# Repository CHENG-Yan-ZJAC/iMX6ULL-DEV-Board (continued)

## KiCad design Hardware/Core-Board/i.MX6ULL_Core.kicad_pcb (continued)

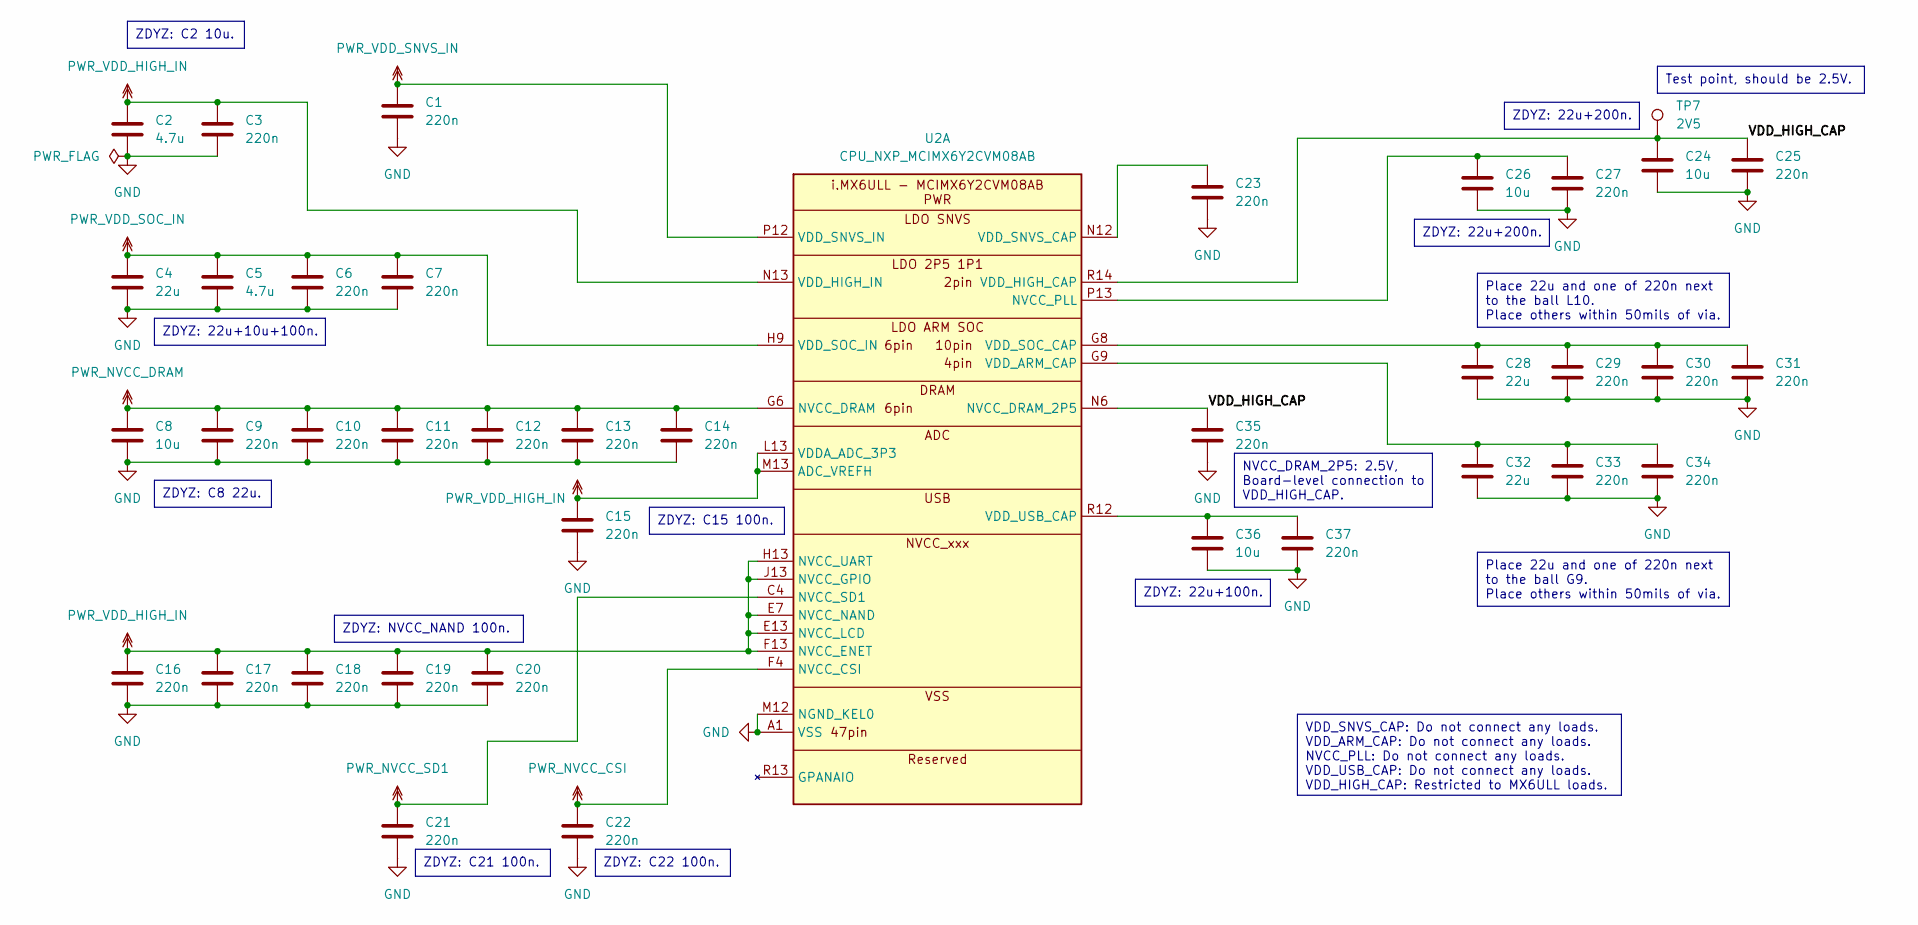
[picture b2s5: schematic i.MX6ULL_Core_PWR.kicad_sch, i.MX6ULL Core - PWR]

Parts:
C1, C3, C6, C7, C9, C10, C11, C12, C13, C14, C15, C16, C17, C18, C19, C20, C21, C22, C23, C25, C27, C29, C30, C31, C33, C34, C35, C37: 220n; C_0402
C2, C5: 4.7u; C_0402
C4, C28, C32: 22u; C_0402
C8, C24, C26, C36: 10u; C_0402
TP7: 2V5; TestPoint_Pad_D1.0mm
U2: CPU_NXP_MCIMX6Y2CVM08AB; NXP_BGA-289_14x14mm_Layout14x14_P0.8mm_Ball0.45mm_Pad0.4mm

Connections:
/PWR/VDD_HIGH_CAP: C24.2, C25.2, C35.2, TP7.1, U2.N6 (NVCC_DRAM_2P5), U2.R14 (VDD_HIGH_CAP), U2.R15 (VDD_HIGH_CAP)
GND: C1.2, C2.1, C3.1, C4.1, C5.1, C6.1, C7.2, C8.1, C9.1, C10.1, C11.1, C12.1, C13.1, C14.1, C15.1, C16.1, C17.2, C18.2, C19.2, C20.2, C21.2, C22.2, C23.1, C24.1, C25.1, C26.2, C27.2, C28.2, C29.2, C30.2, C31.2, C32.1, C33.1, C34.1, C35.1, C36.2, C37.2, U2.A1 (VSS), U2.A17 (VSS), U2.C3 (VSS), U2.C7 (VSS), U2.C11 (VSS), U2.C15 (VSS), U2.E8 (VSS), U2.E11 (VSS), U2.F6 (VSS), U2.F7 (VSS), U2.F8 (VSS), U2.F9 (VSS), U2.F10 (VSS), U2.F11 (VSS), U2.F12 (VSS), U2.G3 (VSS), U2.G5 (VSS), U2.G7 (VSS), U2.G12 (VSS), U2.G15 (VSS), U2.H7 (VSS), U2.H12 (VSS), U2.J5 (VSS), U2.J7 (VSS), U2.J12 (VSS), U2.K7 (VSS), U2.K12 (VSS), U2.L3 (VSS), U2.L7 (VSS), U2.L12 (VSS), U2.M7 (VSS), U2.M8 (VSS), U2.M9 (VSS), U2.M10 (VSS), U2.M11 (VSS), U2.M12 (NGND_KEL0), U2.N3 (VSS), U2.N5 (VSS), U2.R3 (VSS), U2.R5 (VSS), U2.R7 (VSS), U2.R11 (VSS), U2.R16 (VSS), U2.R17 (VSS), U2.T14 (VSS), U2.U1 (VSS), U2.U14 (VSS), U2.U17 (VSS); also elsewhere on the board
unnamed: C28.1, C29.1, C30.1, C31.1, U2.G8 (VDD_SOC_CAP), U2.H8 (VDD_SOC_CAP), U2.J8 (VDD_SOC_CAP), U2.J11 (VDD_SOC_CAP), U2.K8 (VDD_SOC_CAP), U2.K11 (VDD_SOC_CAP), U2.L8 (VDD_SOC_CAP), U2.L9 (VDD_SOC_CAP), U2.L10 (VDD_SOC_CAP), U2.L11 (VDD_SOC_CAP)
unnamed: C32.2, C33.2, C34.2, U2.G9 (VDD_ARM_CAP), U2.G10 (VDD_ARM_CAP), U2.G11 (VDD_ARM_CAP), U2.H11 (VDD_ARM_CAP)
unnamed: C26.1, C27.1, U2.P13 (NVCC_PLL)
unnamed: C23.2, U2.N12 (VDD_SNVS_CAP)
unnamed: C36.1, C37.1, U2.R12 (VDD_USB_CAP)
PWR_NVCC_CSI: C22.1, U2.F4 (NVCC_CSI); also elsewhere on the board
PWR_NVCC_DRAM: C8.2, C9.2, C10.2, C11.2, C12.2, C13.2, C14.2, U2.G6 (NVCC_DRAM), U2.H6 (NVCC_DRAM), U2.J6 (NVCC_DRAM), U2.K6 (NVCC_DRAM), U2.L6 (NVCC_DRAM), U2.M6 (NVCC_DRAM); also elsewhere on the board
PWR_NVCC_SD1: C21.1, U2.C4 (NVCC_SD1); also elsewhere on the board
PWR_VDD_HIGH_IN: C2.2, C3.2, C15.2, C16.2, C17.1, C18.1, C19.1, C20.1, U2.E7 (NVCC_NAND), U2.E13 (NVCC_LCD), U2.F13 (NVCC_ENET), U2.H13 (NVCC_UART), U2.J13 (NVCC_GPIO), U2.L13 (VDDA_ADC_3P3), U2.M13 (ADC_VREFH), U2.N13 (VDD_HIGH_IN); also elsewhere on the board
PWR_VDD_SNVS_IN: C1.1, U2.P12 (VDD_SNVS_IN); also elsewhere on the board
PWR_VDD_SOC_IN: C4.2, C5.2, C6.2, C7.1, U2.H9 (VDD_SOC_IN), U2.H10 (VDD_SOC_IN), U2.J9 (VDD_SOC_IN), U2.J10 (VDD_SOC_IN), U2.K9 (VDD_SOC_IN), U2.K10 (VDD_SOC_IN); also elsewhere on the board

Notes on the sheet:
ZDYZ: 22u+10u+100n.
NVCC_DRAM_2P5: 2.5V, Board-level connection to VDD_HIGH_CAP.
ZDYZ: C15 100n.
ZDYZ: C22 100n.
ZDYZ: C21 100n.
VDD_SNVS_CAP: Do not connect any loads. VDD_ARM_CAP: Do not connect any loads. NVCC_PLL: Do not connect any loads. VDD_USB_CAP: Do not connect any loads. VDD_HIGH_CAP: Restricted to MX6ULL loads.
ZDYZ: C2 10u.
ZDYZ: NVCC_NAND 100n.
ZDYZ: 22u+200n.
ZDYZ: 22u+100n.
Place 22u and one of 220n next to the ball L10. Place others within 50mils of via.
Place 22u and one of 220n next to the ball G9. Place others within 50mils of via.
ZDYZ: C8 22u.
Test point, should be 2.5V.

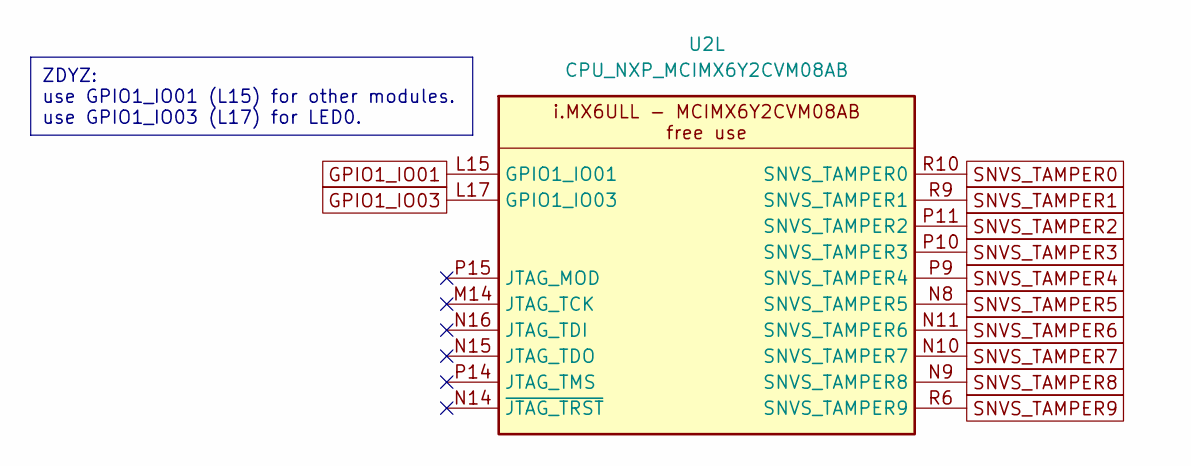
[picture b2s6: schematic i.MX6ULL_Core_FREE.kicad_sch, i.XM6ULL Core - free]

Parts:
U2: CPU_NXP_MCIMX6Y2CVM08AB; NXP_BGA-289_14x14mm_Layout14x14_P0.8mm_Ball0.45mm_Pad0.4mm

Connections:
GPIO1_IO01: U2.L15 (GPIO1_IO01); also elsewhere on the board
GPIO1_IO03: U2.L17 (GPIO1_IO03); also elsewhere on the board
SNVS_TAMPER0: U2.R10 (SNVS_TAMPER0); also elsewhere on the board
SNVS_TAMPER1: U2.R9 (SNVS_TAMPER1); also elsewhere on the board
SNVS_TAMPER2: U2.P11 (SNVS_TAMPER2); also elsewhere on the board
SNVS_TAMPER3: U2.P10 (SNVS_TAMPER3); also elsewhere on the board
SNVS_TAMPER4: U2.P9 (SNVS_TAMPER4); also elsewhere on the board
SNVS_TAMPER5: U2.N8 (SNVS_TAMPER5); also elsewhere on the board
SNVS_TAMPER6: U2.N11 (SNVS_TAMPER6); also elsewhere on the board
SNVS_TAMPER7: U2.N10 (SNVS_TAMPER7); also elsewhere on the board
SNVS_TAMPER8: U2.N9 (SNVS_TAMPER8); also elsewhere on the board
SNVS_TAMPER9: U2.R6 (SNVS_TAMPER9); also elsewhere on the board

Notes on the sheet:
ZDYZ: use GPIO1_IO01 (L15) for other modules. use GPIO1_IO03 (L17) for LED0.

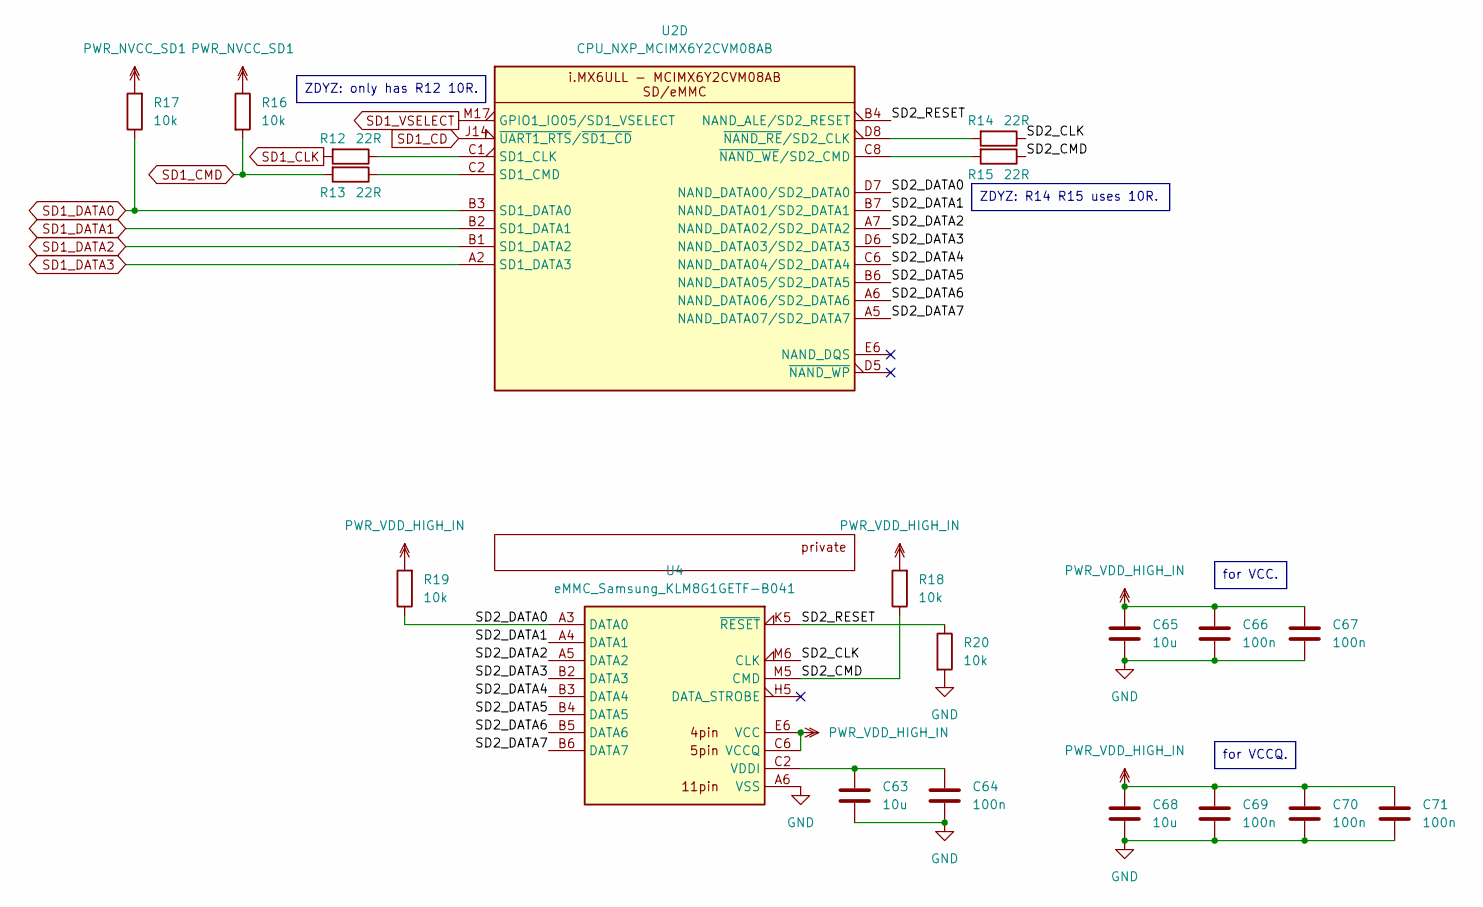
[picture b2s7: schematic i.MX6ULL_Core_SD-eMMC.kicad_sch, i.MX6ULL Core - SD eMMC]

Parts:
C63, C65, C68: 10u; C_0402
C64, C66, C67, C69, C70, C71: 100n; C_0402
R12, R13, R14, R15: 22R; R_0402
R16, R17, R18, R19, R20: 10k; R_0402
U2: CPU_NXP_MCIMX6Y2CVM08AB; NXP_BGA-289_14x14mm_Layout14x14_P0.8mm_Ball0.45mm_Pad0.4mm
U4: eMMC_Samsung_KLM8G1GETF-B041; Samsung_BGA-153_11.5x13mm_Layout11.5x13_P0.5mm_Ball0.3mm_Pa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

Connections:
/SD-eMMC/SD2_CLK: R14.1, U4.M6 (CLK)
/SD-eMMC/SD2_CMD: R15.1, R18.1, U4.M5 (CMD)
/SD-eMMC/SD2_DATA0: R19.1, U2.D7 (NAND_DATA00/SD2_DATA0), U4.A3 (DATA0)
/SD-eMMC/SD2_DATA1: U2.B7 (NAND_DATA01/SD2_DATA1), U4.A4 (DATA1)
/SD-eMMC/SD2_DATA2: U2.A7 (NAND_DATA02/SD2_DATA2), U4.A5 (DATA2)
/SD-eMMC/SD2_DATA3: U2.D6 (NAND_DATA03/SD2_DATA3), U4.B2 (DATA3)
/SD-eMMC/SD2_DATA4: U2.C6 (NAND_DATA04/SD2_DATA4), U4.B3 (DATA4)
/SD-eMMC/SD2_DATA5: U2.B6 (NAND_DATA05/SD2_DATA5), U4.B4 (DATA5)
/SD-eMMC/SD2_DATA6: U2.A6 (NAND_DATA06/SD2_DATA6), U4.B5 (DATA6)
/SD-eMMC/SD2_DATA7: U2.A5 (NAND_DATA07/SD2_DATA7), U4.B6 (DATA7)
/SD-eMMC/SD2_RESET: R20.1, U2.B4 (NAND_ALE/SD2_RESET), U4.K5 (~RESET)
GND: C63.2, C64.2, C65.2, C66.2, C67.2, C68.2, C69.2, C70.2, C71.2, R20.2, U4.A6 (VSS), U4.C4 (VSS), U4.E7 (VSS), U4.G5 (VSS), U4.H10 (VSS), U4.J5 (VSS), U4.K8 (VSS), U4.N2 (VSS), U4.N5 (VSS), U4.P4 (VSS), U4.P6 (VSS); also elsewhere on the board
unnamed: R12.1, U2.C1 (SD1_CLK)
unnamed: R13.1, U2.C2 (SD1_CMD)
unnamed: R14.2, U2.D8 (~NAND_RE/SD2_CLK)
unnamed: R15.2, U2.C8 (~NAND_WE/SD2_CMD)
unnamed: C63.1, C64.1, U4.C2 (VDDI)
PWR_NVCC_SD1: R16.1, R17.2; also elsewhere on the board
PWR_VDD_HIGH_IN: C65.1, C66.1, C67.1, C68.1, C69.1, C70.1, C71.1, R18.2, R19.2, U4.C6 (VCCQ), U4.E6 (VCC), U4.F5 (VCC), U4.J10 (VCC), U4.K9 (VCC), U4.M4 (VCCQ), U4.N4 (VCCQ), U4.P3 (VCCQ), U4.P5 (VCCQ); also elsewhere on the board
SD1_CD: U2.J14 (~UART1_RTS/~SD1_CD); also elsewhere on the board
SD1_CLK: R12.2; also elsewhere on the board
SD1_CMD: R13.2, R16.2; also elsewhere on the board
SD1_DATA0: R17.1, U2.B3 (SD1_DATA0); also elsewhere on the board
SD1_DATA1: U2.B2 (SD1_DATA1); also elsewhere on the board
SD1_DATA2: U2.B1 (SD1_DATA2); also elsewhere on the board
SD1_DATA3: U2.A2 (SD1_DATA3); also elsewhere on the board
SD1_VSELECT: U2.M17 (GPIO1_IO05/SD1_VSELECT); also elsewhere on the board

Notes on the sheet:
for VCC.
ZDYZ: only has R12 10R.
for VCCQ.
ZDYZ: R14 R15 uses 10R.

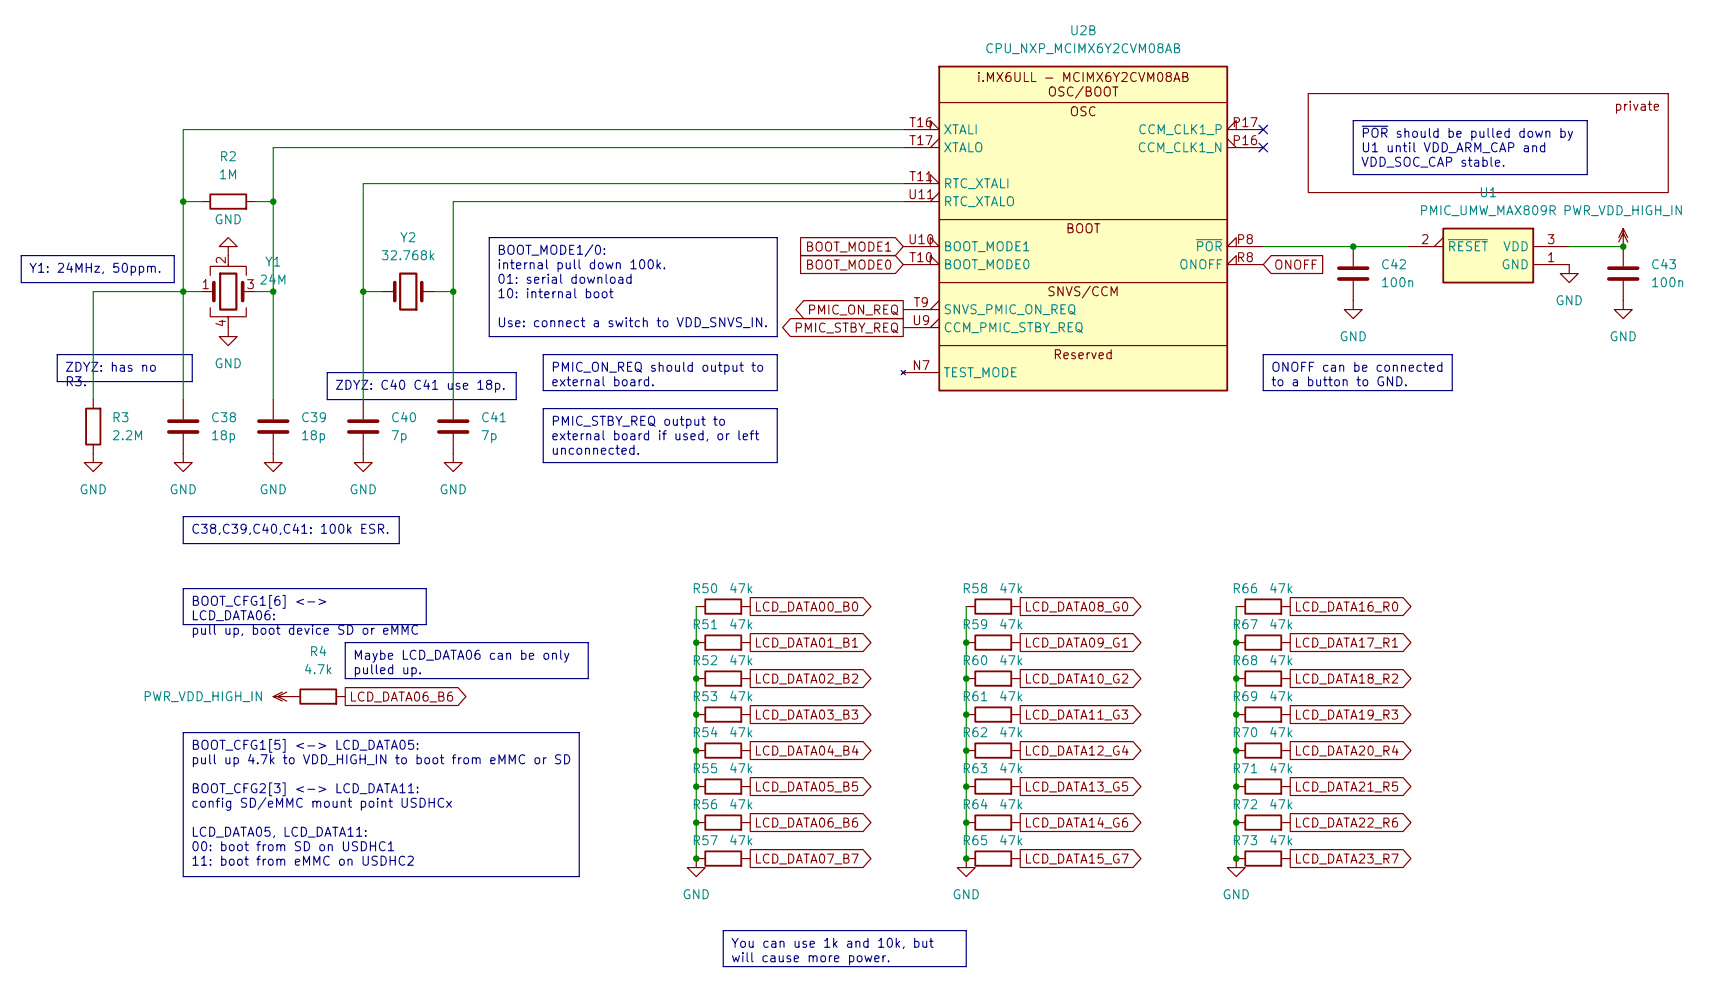
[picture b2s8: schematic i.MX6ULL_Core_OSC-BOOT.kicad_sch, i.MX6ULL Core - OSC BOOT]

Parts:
C38, C39: 18p; C_0402
C40, C41: 7p; C_0402
C42, C43: 100n; C_0402
R2: 1M; R_0402
R3: 2.2M; R_0402
R4: 4.7k; R_0402
R50, R51, R52, R53, R54, R55, R56, R57, R58, R59, R60, R61, R62, R63, R64, R65, R66, R67, R68, R69, R70, R71, R72, R73: 47k; R_0402
U1: PMIC_UMW_MAX809R; SOT_23
U2: CPU_NXP_MCIMX6Y2CVM08AB; NXP_BGA-289_14x14mm_Layout14x14_P0.8mm_Ball0.45mm_Pad0.4mm
Y1: 24M; Crystal_SMD_3225-4Pin_3.2x2.5mm
Y2: 32.768k; Crystal_SMD_3215-2Pin_3.2x1.5mm

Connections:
BOOT_MODE0: U2.T10 (BOOT_MODE0); also elsewhere on the board
BOOT_MODE1: U2.U10 (BOOT_MODE1); also elsewhere on the board
GND: C38.1, C39.2, C40.1, C41.2, C42.2, C43.1, R3.1, R50.1, R51.1, R52.1, R53.1, R54.1, R55.1, R56.1, R57.1, R58.1, R59.1, R60.1, R61.1, R62.1, R63.1, R64.1, R65.1, R66.1, R67.1, R68.1, R69.1, R70.1, R71.1, R72.1, R73.1, U1.1 (GND), Y1.2, Y1.4; also elsewhere on the board
LCD_DATA00_B0: R50.2; also elsewhere on the board
LCD_DATA01_B1: R51.2; also elsewhere on the board
LCD_DATA02_B2: R52.2; also elsewhere on the board
LCD_DATA03_B3: R53.2; also elsewhere on the board
LCD_DATA04_B4: R54.2; also elsewhere on the board
LCD_DATA05_B5: R55.2; also elsewhere on the board
LCD_DATA06_B6: R4.2, R56.2; also elsewhere on the board
LCD_DATA07_B7: R57.2; also elsewhere on the board
LCD_DATA08_G0: R58.2; also elsewhere on the board
LCD_DATA09_G1: R59.2; also elsewhere on the board
LCD_DATA10_G2: R60.2; also elsewhere on the board
LCD_DATA11_G3: R61.2; also elsewhere on the board
LCD_DATA12_G4: R62.2; also elsewhere on the board
LCD_DATA13_G5: R63.2; also elsewhere on the board
LCD_DATA14_G6: R64.2; also elsewhere on the board
LCD_DATA15_G7: R65.2; also elsewhere on the board
LCD_DATA16_R0: R66.2; also elsewhere on the board
LCD_DATA17_R1: R67.2; also elsewhere on the board
LCD_DATA18_R2: R68.2; also elsewhere on the board
LCD_DATA19_R3: R69.2; also elsewhere on the board
LCD_DATA20_R4: R70.2; also elsewhere on the board
LCD_DATA21_R5: R71.2; also elsewhere on the board
LCD_DATA22_R6: R72.2; also elsewhere on the board
LCD_DATA23_R7: R73.2; also elsewhere on the board
unnamed: C42.1, U1.2 (~RESET), U2.P8 (~POR)
unnamed: C40.2, U2.T11 (RTC_XTALI), Y2.2
unnamed: C41.1, U2.U11 (RTC_XTALO), Y2.1
unnamed: C38.2, R2.1, R3.2, U2.T16 (XTALI), Y1.1
unnamed: C39.1, R2.2, U2.T17 (XTALO), Y1.3
ONOFF: U2.R8 (ONOFF); also elsewhere on the board
PMIC_ON_REQ: U2.T9 (SNVS_PMIC_ON_REQ); also elsewhere on the board
PMIC_STBY_REQ: U2.U9 (CCM_PMIC_STBY_REQ); also elsewhere on the board
PWR_VDD_HIGH_IN: C43.2, R4.1, U1.3 (VDD); also elsewhere on the board

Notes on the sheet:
ONOFF can be connected to a button to GND.
BOOT_MODE1/0: internal pull down 100k. 01: serial download 10: internal boot Use: connect a switch to VDD_SNVS_IN.
ZDYZ: has no R3.
BOOT_CFG1[5] <-> LCD_DATA05: pull up 4.7k to VDD_HIGH_IN to boot from eMMC or SD BOOT_CFG2[3] <-> LCD_DATA11: config SD/eMMC mount point USDHCx LCD_DATA05, LCD_DATA11: 00: boot from SD on USDHC1 11: boot from eMMC on USDHC2
Y1: 24MHz, 50ppm.
You can use 1k and 10k, but will cause more power.
BOOT_CFG1[6] <-> LCD_DATA06: pull up, boot device SD or eMMC
Maybe LCD_DATA06 can be only pulled up.
PMIC_STBY_REQ output to external board if used, or left unconnected.
ZDYZ: C40 C41 use 18p.
~{POR} should be pulled down by U1 until VDD_ARM_CAP and VDD_SOC_CAP stable.
PMIC_ON_REQ should output to external board.
C38,C39,C40,C41: 100k ESR.

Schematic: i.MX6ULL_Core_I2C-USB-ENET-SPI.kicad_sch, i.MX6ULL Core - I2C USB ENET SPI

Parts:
C72, C73: 1u; C_0402
R22, R23: 10R; R_0402
U2: CPU_NXP_MCIMX6Y2CVM08AB; NXP_BGA-289_14x14mm_Layout14x14_P0.8mm_Ball0.45mm_Pad0.4mm

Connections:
ECSPI3_MISO: U2.A4 (ECSPI3_MISO/NAND_CLE); also elsewhere on the board
ECSPI3_MOSI: U2.B5 (ECSPI3_MOSI/~NAND_CE1); also elsewhere on the board
ECSPI3_SCLK: U2.C5 (ECSPI3_SCLK/~NAND_CE0); also elsewhere on the board
ECSPI3_SS0: U2.A3 (ECSPI3_SS0/~NAND_READY); also elsewhere on the board
ENET1_INT: U2.G14 (GOIO1_IO27/~UART3_RTS); also elsewhere on the board
ENET1_RESET: U2.H14 (GPIO1_IO23/~UART2_RTS); also elsewhere on the board
ENET1_RX_DATA0: U2.F16 (ENET1_RX_DATA0); also elsewhere on the board
ENET1_RX_DATA1: U2.E17 (ENET1_RX_DATA1); also elsewhere on the board
ENET1_RX_EN: U2.E16 (ENET1_RX_EN); also elsewhere on the board
ENET1_RX_ER: U2.D15 (ENET1_RX_ER); also elsewhere on the board
ENET1_TX_CLK: R22.1; also elsewhere on the board
ENET1_TX_DATA0: U2.E15 (ENET1_TX_DATA0); also elsewhere on the board
ENET1_TX_DATA1: U2.E14 (ENET1_TX_DATA1); also elsewhere on the board
ENET1_TX_EN: U2.F15 (ENET1_TX_EN); also elsewhere on the board
ENET2_INT: U2.H15 (~UART3_CTS/GPIO1_IO26); also elsewhere on the board
ENET2_RESET: U2.J15 (~UART2_CTS/GPIO1_IO22); also elsewhere on the board
ENET2_RX_DATA0: U2.C17 (ENET2_RX_DATA0); also elsewhere on the board
ENET2_RX_DATA1: U2.C16 (ENET2_RX_DATA1); also elsewhere on the board
ENET2_RX_EN: U2.B17 (ENET2_RX_EN); also elsewhere on the board
ENET2_RX_ER: U2.D16 (ENET2_RX_ER); also elsewhere on the board
ENET2_TX_CLK: R23.1; also elsewhere on the board
ENET2_TX_DATA0: U2.A15 (ENET2_TX_DATA0); also elsewhere on the board
ENET2_TX_DATA1: U2.A16 (ENET2_TX_DATA1); also elsewhere on the board
ENET2_TX_EN: U2.B15 (ENET2_TX_EN); also elsewhere on the board
ENET_MDC: U2.L16 (ENET_MDC/GPIO1_IO07); also elsewhere on the board
ENET_MDIO: U2.K17 (ENET_MDIO/GPIO1_IO06); also elsewhere on the board
GND: C72.2, C73.2; also elsewhere on the board
I2C1_CLK: U2.G17 (I2C1_CLK/UART4_TXD); also elsewhere on the board
I2C1_SDA: U2.G16 (I2C1_SDA/UART4_RXD); also elsewhere on the board
I2C2_CLK: U2.F17 (UART5_TXD/I2C2_CLK); also elsewhere on the board
I2C2_SDA: U2.G13 (UART5_RXD/I2C2_SDA); also elsewhere on the board
unnamed: R22.2, U2.F14 (ENET1_TX_CLK)
unnamed: R23.2, U2.D17 (ENET2_TX_CLK)
USB_OTG1_DN: U2.T15 (USB_OTG1_DN); also elsewhere on the board
USB_OTG1_DP: U2.U15 (USB_OTG1_DP); also elsewhere on the board
USB_OTG1_ID: U2.K13 (ANATOP_OTG1_ID/GPIO1_IO00); also elsewhere on the board
USB_OTG1_VBUS: C72.1, U2.T12 (USB_OTG1_VBUS); also elsewhere on the board
USB_OTG2_DN: U2.T13 (USB_OTG2_DN); also elsewhere on the board
USB_OTG2_DP: U2.U13 (USB_OTG2_DP); also elsewhere on the board
USB_OTG2_VBUS: C73.1, U2.U12 (USB_OTG2_VBUS); also elsewhere on the board

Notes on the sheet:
ZDYZ: use SNVS_TAMPER8 (N9) for ENET2_RESET. use SNVS_TAMPER6 (N11) for ENET2_INT.
ZDYZ: C73 100n.
C72,C73: 1uF, 10V rated.
ZDYZ: C72 100n.
ZDYZ: use SNVS_TAMPER7 (N10) for ENET1_RESET. use SNVS_TAMPER5 (N8) for ENET1_INT.

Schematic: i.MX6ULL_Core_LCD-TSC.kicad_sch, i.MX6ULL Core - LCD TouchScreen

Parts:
R21: 10R; R_0402
U2: CPU_NXP_MCIMX6Y2CVM08AB; NXP_BGA-289_14x14mm_Layout14x14_P0.8mm_Ball0.45mm_Pad0.4mm

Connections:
LCD_BL_PWM: U2.N17 (GPIO1_IO08/PWM1_OUT); also elsewhere on the board
LCD_CLK: R21.1; also elsewhere on the board
LCD_DATA00_B0: U2.B9 (LCD_DATA00); also elsewhere on the board
LCD_DATA01_B1: U2.A9 (LCD_DATA01); also elsewhere on the board
LCD_DATA02_B2: U2.E10 (LCD_DATA02); also elsewhere on the board
LCD_DATA03_B3: U2.D10 (LCD_DATA03); also elsewhere on the board
LCD_DATA04_B4: U2.C10 (LCD_DATA04); also elsewhere on the board
LCD_DATA05_B5: U2.B10 (LCD_DATA05); also elsewhere on the board
LCD_DATA06_B6: U2.A10 (LCD_DATA06); also elsewhere on the board
LCD_DATA07_B7: U2.D11 (LCD_DATA07); also elsewhere on the board
LCD_DATA08_G0: U2.B11 (LCD_DATA08); also elsewhere on the board
LCD_DATA09_G1: U2.A11 (LCD_DATA09); also elsewhere on the board
LCD_DATA10_G2: U2.E12 (LCD_DATA10); also elsewhere on the board
LCD_DATA11_G3: U2.D12 (LCD_DATA11); also elsewhere on the board
LCD_DATA12_G4: U2.C12 (LCD_DATA12); also elsewhere on the board
LCD_DATA13_G5: U2.B12 (LCD_DATA13); also elsewhere on the board
LCD_DATA14_G6: U2.A12 (LCD_DATA14); also elsewhere on the board
LCD_DATA15_G7: U2.D13 (LCD_DATA15); also elsewhere on the board
LCD_DATA16_R0: U2.C13 (LCD_DATA16); also elsewhere on the board
LCD_DATA17_R1: U2.B13 (LCD_DATA17); also elsewhere on the board
LCD_DATA18_R2: U2.A13 (LCD_DATA18); also elsewhere on the board
LCD_DATA19_R3: U2.D14 (LCD_DATA19); also elsewhere on the board
LCD_DATA20_R4: U2.C14 (LCD_DATA20); also elsewhere on the board
LCD_DATA21_R5: U2.B14 (LCD_DATA21); also elsewhere on the board
LCD_DATA22_R6: U2.A14 (LCD_DATA22); also elsewhere on the board
LCD_DATA23_R7: U2.B16 (LCD_DATA23); also elsewhere on the board
LCD_ENABLE: U2.B8 (LCD_ENABLE); also elsewhere on the board
LCD_HSYNC: U2.D9 (LCD_HSYNC); also elsewhere on the board
LCD_RESET: U2.E9 (LCD_RESET); also elsewhere on the board
LCD_VSYNC: U2.C9 (LCD_VSYNC); also elsewhere on the board
unnamed: R21.2, U2.A8 (LCD_CLK)
TSC_INT: U2.M15 (GPIO1_IO09); also elsewhere on the board
TSC_RESET: U2.L14 (GPIO1_IO02); also elsewhere on the board

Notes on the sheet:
ZDYZ: use LCD_RESET (E9) for reset DCDC_3V3.
ZDYZ: use SNVS_TAMPER9 (R6) for TSC_RESET.

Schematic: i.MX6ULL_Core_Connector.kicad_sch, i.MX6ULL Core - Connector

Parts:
J1: SODIMM-260_DDR4; SODIMM-260_DDR4_Card_edge
M1, M2, M3, M4, M5, M6, M7, M8: MARK_D1.0mm

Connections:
BOOT_MODE0: J1.15; also elsewhere on the board
BOOT_MODE1: J1.17; also elsewhere on the board
CSI_DATA00: J1.106; also elsewhere on the board
CSI_DATA01: J1.110; also elsewhere on the board
CSI_DATA02: J1.112; also elsewhere on the board
CSI_DATA03: J1.108; also elsewhere on the board
CSI_DATA04: J1.104; also elsewhere on the board
CSI_DATA05: J1.100; also elsewhere on the board
CSI_DATA06: J1.98; also elsewhere on the board
CSI_DATA07: J1.94; also elsewhere on the board
CSI_HSYNC: J1.92; also elsewhere on the board
CSI_MCLK: J1.96; also elsewhere on the board
CSI_PIXCLK: J1.102; also elsewhere on the board
CSI_PWDN: J1.90; also elsewhere on the board
CSI_RESET: J1.86; also elsewhere on the board
CSI_VSYNC: J1.88; also elsewhere on the board
ECSPI3_MISO: J1.244; also elsewhere on the board
ECSPI3_MOSI: J1.242; also elsewhere on the board
ECSPI3_SCLK: J1.248; also elsewhere on the board
ECSPI3_SS0: J1.246; also elsewhere on the board
ENET1_INT: J1.66; also elsewhere on the board
ENET1_RESET: J1.64; also elsewhere on the board
ENET1_RX_DATA0: J1.72; also elsewhere on the board
ENET1_RX_DATA1: J1.70; also elsewhere on the board
ENET1_RX_EN: J1.74; also elsewhere on the board
ENET1_RX_ER: J1.82; also elsewhere on the board
ENET1_TX_CLK: J1.68; also elsewhere on the board
ENET1_TX_DATA0: J1.78; also elsewhere on the board
ENET1_TX_DATA1: J1.80; also elsewhere on the board
ENET1_TX_EN: J1.76; also elsewhere on the board
ENET2_INT: J1.65; also elsewhere on the board
ENET2_RESET: J1.63; also elsewhere on the board
ENET2_RX_DATA0: J1.71; also elsewhere on the board
ENET2_RX_DATA1: J1.73; also elsewhere on the board
ENET2_RX_EN: J1.75; also elsewhere on the board
ENET2_RX_ER: J1.69; also elsewhere on the board
ENET2_TX_CLK: J1.67; also elsewhere on the board
ENET2_TX_DATA0: J1.81; also elsewhere on the board
ENET2_TX_DATA1: J1.79; also elsewhere on the board
ENET2_TX_EN: J1.77; also elsewhere on the board
ENET_MDC: J1.59; also elsewhere on the board
ENET_MDIO: J1.61; also elsewhere on the board
GND: J1.21, J1.22, J1.27, J1.28, J1.207, J1.209, J1.211, J1.213, J1.215, J1.217, J1.219, J1.221, J1.223, J1.225, J1.227, J1.229, J1.231, J1.233, J1.235, J1.237; also elsewhere on the board
GPIO1_IO01: J1.54; also elsewhere on the board
GPIO1_IO03: J1.56; also elsewhere on the board
I2C1_CLK: J1.34; also elsewhere on the board
I2C1_SDA: J1.32; also elsewhere on the board
I2C2_CLK: J1.38; also elsewhere on the board
I2C2_SDA: J1.36; also elsewhere on the board
LCD_BL_PWM: J1.121; also elsewhere on the board
LCD_CLK: J1.179; also elsewhere on the board
LCD_DATA00_B0: J1.171; also elsewhere on the board
LCD_DATA01_B1: J1.169; also elsewhere on the board
LCD_DATA02_B2: J1.167; also elsewhere on the board
LCD_DATA03_B3: J1.165; also elsewhere on the board
LCD_DATA04_B4: J1.163; also elsewhere on the board
LCD_DATA05_B5: J1.161; also elsewhere on the board
LCD_DATA06_B6: J1.159; also elsewhere on the board
LCD_DATA07_B7: J1.157; also elsewhere on the board
LCD_DATA08_G0: J1.155; also elsewhere on the board
LCD_DATA09_G1: J1.153; also elsewhere on the board
LCD_DATA10_G2: J1.151; also elsewhere on the board
LCD_DATA11_G3: J1.149; also elsewhere on the board
LCD_DATA12_G4: J1.147; also elsewhere on the board
LCD_DATA13_G5: J1.145; also elsewhere on the board
LCD_DATA14_G6: J1.143; also elsewhere on the board
LCD_DATA15_G7: J1.141; also elsewhere on the board
LCD_DATA16_R0: J1.139; also elsewhere on the board
LCD_DATA17_R1: J1.137; also elsewhere on the board
LCD_DATA18_R2: J1.135; also elsewhere on the board
LCD_DATA19_R3: J1.133; also elsewhere on the board
LCD_DATA20_R4: J1.131; also elsewhere on the board
LCD_DATA21_R5: J1.129; also elsewhere on the board
LCD_DATA22_R6: J1.127; also elsewhere on the board
LCD_DATA23_R7: J1.125; also elsewhere on the board
LCD_ENABLE: J1.173; also elsewhere on the board
LCD_HSYNC: J1.177; also elsewhere on the board
LCD_RESET: J1.123; also elsewhere on the board
LCD_VSYNC: J1.175; also elsewhere on the board
ONOFF: J1.14; also elsewhere on the board
PMIC_ON_REQ: J1.18; also elsewhere on the board
PMIC_STBY_REQ: J1.16; also elsewhere on the board
PWR_NVCC_CSI: J1.220; also elsewhere on the board
PWR_NVCC_DRAM: J1.226, J1.228, J1.230; also elsewhere on the board
PWR_NVCC_SD1: J1.222; also elsewhere on the board
PWR_VDD_HIGH_IN: J1.234, J1.236, J1.238; also elsewhere on the board
PWR_VDD_SNVS_IN: J1.208; also elsewhere on the board
PWR_VDD_SOC_IN: J1.212, J1.214, J1.216; also elsewhere on the board
SD1_CD: J1.241; also elsewhere on the board
SD1_CLK: J1.247; also elsewhere on the board
SD1_CMD: J1.249; also elsewhere on the board
SD1_DATA0: J1.245; also elsewhere on the board
SD1_DATA1: J1.243; also elsewhere on the board
SD1_DATA2: J1.253; also elsewhere on the board
SD1_DATA3: J1.251; also elsewhere on the board
SD1_VSELECT: J1.204; also elsewhere on the board
SNVS_TAMPER0: J1.49; also elsewhere on the board
SNVS_TAMPER1: J1.47; also elsewhere on the board
SNVS_TAMPER2: J1.51; also elsewhere on the board
SNVS_TAMPER3: J1.46; also elsewhere on the board
SNVS_TAMPER4: J1.44; also elsewhere on the board
SNVS_TAMPER5: J1.42; also elsewhere on the board
SNVS_TAMPER6: J1.50; also elsewhere on the board
SNVS_TAMPER7: J1.48; also elsewhere on the board
SNVS_TAMPER8: J1.52; also elsewhere on the board
SNVS_TAMPER9: J1.45; also elsewhere on the board
TSC_INT: J1.119; also elsewhere on the board
TSC_RESET: J1.117; also elsewhere on the board
UART1_RXD: J1.31; also elsewhere on the board
UART1_TXD: J1.33; also elsewhere on the board
UART2_RXD: J1.37; also elsewhere on the board
UART2_TXD: J1.35; also elsewhere on the board
UART3_RXD: J1.41; also elsewhere on the board
UART3_TXD: J1.39; also elsewhere on the board
USB_OTG1_DN: J1.25; also elsewhere on the board
USB_OTG1_DP: J1.23; also elsewhere on the board
USB_OTG1_ID: J1.29; also elsewhere on the board
USB_OTG1_VBUS: J1.19; also elsewhere on the board
USB_OTG2_DN: J1.26; also elsewhere on the board
USB_OTG2_DP: J1.24; also elsewhere on the board
USB_OTG2_VBUS: J1.20; also elsewhere on the board

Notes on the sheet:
8 marks for SMT.

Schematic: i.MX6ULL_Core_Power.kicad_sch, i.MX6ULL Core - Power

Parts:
D1: LED; LED_0402
R1: 1k; R_0402
TP1, TP2: 3V3; TestPoint_Pad_D1.0mm; not fitted
TP3, TP4: 1V35; TestPoint_Pad_D1.0mm; not fitted
TP5: 2V8; TestPoint_Pad_D1.0mm; not fitted
TP6: 3V3,1V8; TestPoint_Pad_D1.0mm; not fitted

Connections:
GND: D1.1 (K); also elsewhere on the board
unnamed: D1.2 (A), R1.1
PWR_VDD_HIGH_IN: R1.2, TP2.1; also elsewhere on the board

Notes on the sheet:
DCDC or LDO
DCDC
+5V
LDO
PWR_VDD_SNVS_IN 3.3V always on
PWR_VDD_SOC_IN 1.35V turned on by PWR_VDD_HIGH_IN
PMIC_ON_REQ
PWR_VDD_HIGH_IN 3.3V turned on by PMIC_ON_REQ
PWR_NVCC_CSI 2.8V turned on by PWR_VDD_HIGH_IN OR LDO from PWR_VDD_HIGH_IN
PWR_NVCC_SD1 3.3V/1.8V turned on by PWR_VDD_HIGH_IN controlled by SD1_VSELECT, switch voltage
PWR_NVCC_DRAM 1.35V turned on by PWR_VDD_HIGH_IN

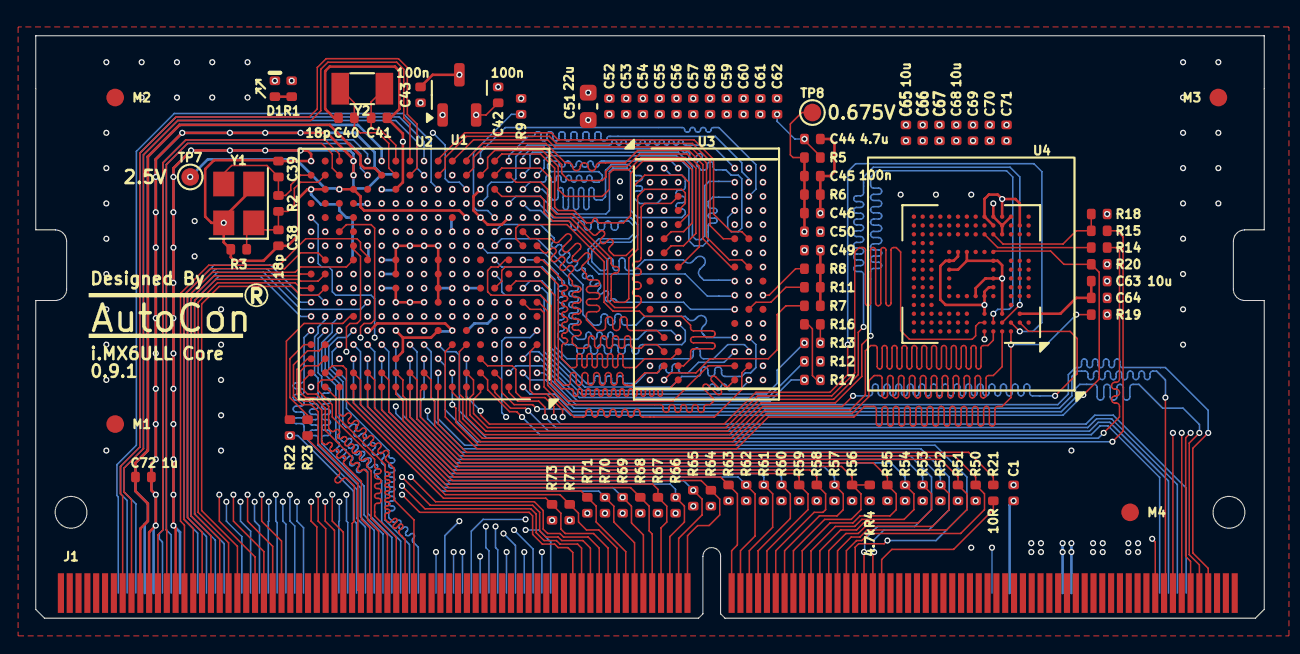
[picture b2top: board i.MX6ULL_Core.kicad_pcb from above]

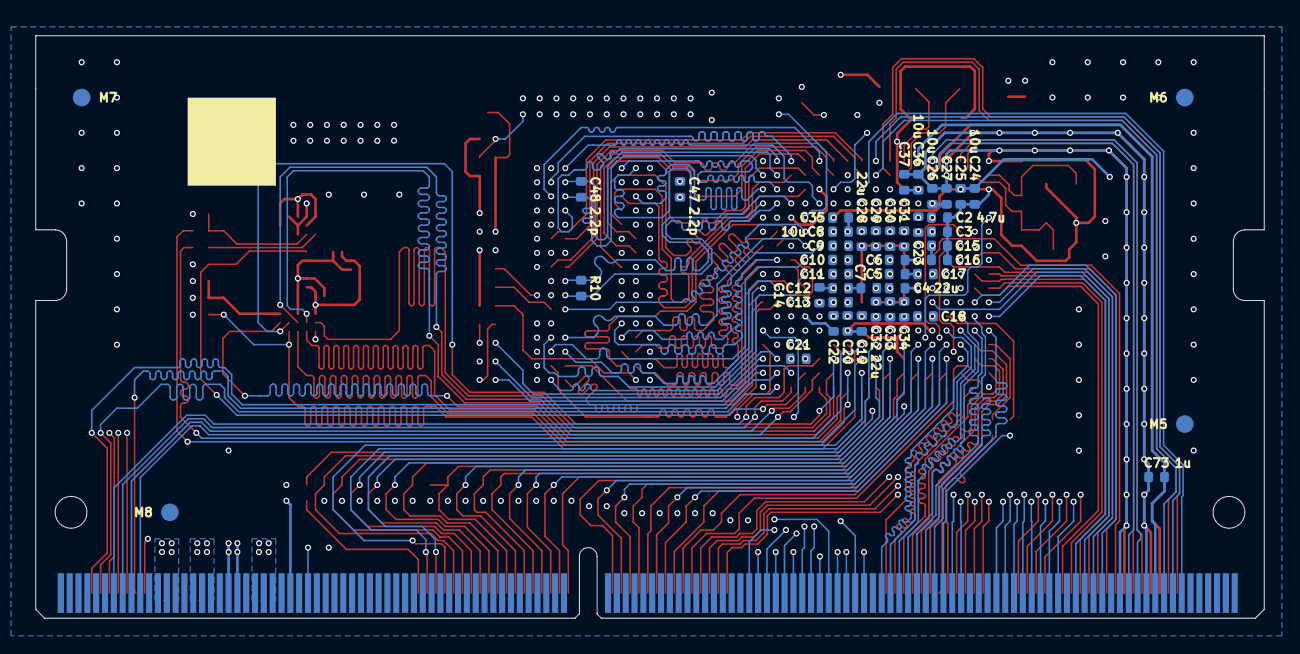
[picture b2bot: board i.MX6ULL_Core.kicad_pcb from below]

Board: 6 copper layers, 69.6 x 33.0 mm, 138 parts (44 on the bottom side), 204 nets.

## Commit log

2024-06-19 Add board image.
2024-06-19 Add hardware.
